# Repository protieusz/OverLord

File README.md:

# OverLord

Lotus layout unified split with 2x mcus & 2x trackballs.

# Sponsorship

Thank you  for sponsoring. For all you PCB/PCBA needs, PCBWay is the way to go. Good quality and customer service. During files submission, PCBWay take the time to check the BOM file and the component placement file to make sure that it is up to specs. If there are any issues, PCBWay will email back and inform the customer if there are any corrections that need to be made and also provide solutions for the customer. I highly recommend PCBWay. 

# Featured On KBDNews
https://kbd.news/OverLord-2477.html

# Detailed Summary

OverLord is a heavily modified version of Noraneko42L which has been blessed by darakuneko himself for the mod. Noraneko42L was originally designed by [darakuneko](https://github.com/darakuneko/Noraneko/tree/main/noraneko42l).

Entire PCB was designed using EasyEDA. ~I will upload a convert PCB file later.~ Be warn, the conversion might not be accurate and you might see a lot of DRC errors in KiCad but in EasyEDA it is ok since I have a working PCB right now.

~Right now at the moment still working out the kinks of getting the 2nd trackball to scroll and the orientation for the main mouse trackball. All the keys are working properly.~

A List Of Mods Made To The Original PCB file by darakuneko:

-Eliminate the extra 6th columns on each sides.

-Two circular holes were created in the middle that can accomodate 2x 25mm trackballs powered by 2x PMW3360 sensors.

-Base of the trackball holders with lens cut out is integrated into the top case with integrated 5mm switch plate. Top case sits flush with pcb.

-Full keyboard case was created to house the PCB.

-OverLord is powered by 2x RP2040 Core - As which you can get from AE.

-Shout out to miketronic from Fingerpunch discord for helping me with the QMK coding from his [BR/KN](https://github.com/miketronic/brkn-keyboard) and modifing the matrix to fit my OverLord. No suppport will be given since I just copy and paste.

-Shout to Doesntfazer of KeyboardDweebs.net for proofing reading and sanity checking my PCB schematic.

-Special thanks to Doesntfazer for fixing my QMK pointing device settings and finally got the scrolling ball to work.

-Use M2 brass hot inserts 3.2mm diameter and 4mm length for the M2 screws to secure the case. I forgot how long is my M2 screws are but they should be greater than 10mm so estimated around 14.6mm. Play around with and buy multiple M2 lenght screws.

-"Eye of Sauron" icon logo embross on the top case was borrowed from [Symbolon from the Noun Project](https://thenounproject.com/icon/eye-of-sauron-1007756/). "Eye of Sauron" logo was used to give it a dark lord theme.

-Both RP2040 Core-A mcus will be "linked" together by header pin wires instead of TRRS connector.

-Heads up if you are using Resin STEP files, resin print did not come out good, since the middle part was warped and the factory recommend to use 3.5mm for the bottom flat case area in order to prevent warping during print. Just use the PLA is more safer. Use the files at your own risk. You can modify the STEP files.

# Production Pics

# Test Fitting

# Renders

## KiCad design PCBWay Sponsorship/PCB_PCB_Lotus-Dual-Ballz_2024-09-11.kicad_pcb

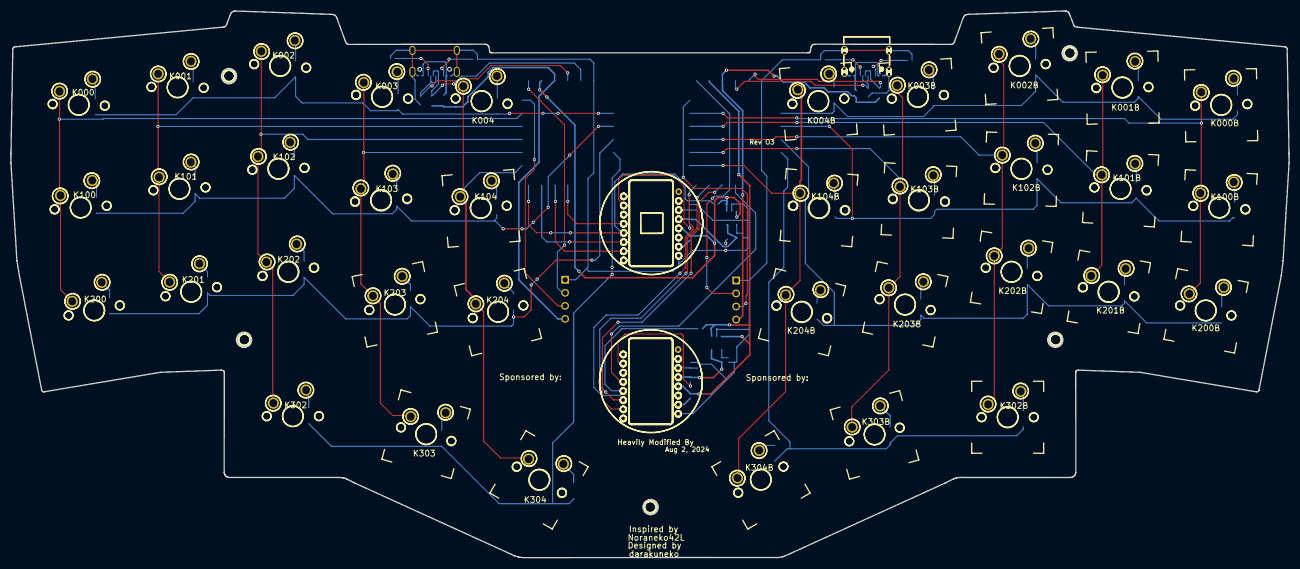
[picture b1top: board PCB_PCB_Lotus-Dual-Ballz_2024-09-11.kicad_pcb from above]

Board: 2 copper layers, 248.7 x 106.4 mm, 108 parts (0 on the bottom side), 92 nets.

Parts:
C17, C17B, C19, C19B, C20, C20B: 4.7uF; C0402
C18, C18B: 100nF; C0402
D000, D000B, D001, D001B, D002, D002B, D003, D003B, D004, D004B, D100, D100B, D101, D101B, D102, D102B, D103, D103B, D104, D104B, D200, D200B, D201, D201B, D202, D202B, D203, D203B, D204, D204B, D302, D302B, D303, D303B, D304, D304B: SM4007PL; SOD-123F_L2.8-W1.8-LS3.7-RD
D5, D11: PRTR5V0U2X,215; SOT-143_L2.9-W1.3-P1.92-LS2.3-BR
F1, F2: BSMD0805-020-15V; F0805
H1, H5: Header pins 1x04 1MM HOLES; 1X04 2.54MM HOLES HEADERS PINS 1MM HOLES
K000, K000B, K001, K001B, K002, K002B, K003, K003B, K004, K004B, K100, K100B, K101, K101B, K102, K102B, K103, K103B, K104, K104B, K200, K200B, K201, K201B, K202, K202B, K203, K203B, K204, K204B, K302, K302B, K303, K303B, K304, K304B: Switch; CHERRY_MX_100_MILLMAX
R1, R2, R3, R4: 5.1kΩ; R0402
R10, R10B, R12, R12B, R13, R13B: 10kΩ; R0402
R11, R11B: 39Ω; R0402
R14, R14B: 15kΩ; R0402
U1, U1B: RP2040-Core-A; RP2040-CORE-A
U7, U7B: PMW3360DM-T2QU; PMW3360DM-T2QU.PACK
U8, U8B: AP2127K-ADJTRG1; SOT-23-5_L3.0-W1.7-P0.95-LS2.8-BR
USBC1, USBC2: TYPE-C-31-M-12; USB-C_SMD-TYPE-C-31-M-12

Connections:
+2V: C20B.2, R11B.2, R14B.2, U7B.4, U8B.5
+2VL: C20.2, R11.2, R14.2, U7.4, U8.5
+3V3: C19B.2, R10B.2, R12B.2, U1B.15, U7B.5, U8B.1, U8B.3
+3V3L: C19.2, R10.2, R12.2, U1.15, U7.5, U8.1, U8.3
+5V: D5.4, F2.2, H1.4, U1B.16
+5VL: D11.4, F1.2, H5.4, U1.16
C18B_1: C17B.1, C18B.1, U7B.3
COL0L: K000.2, K100.2, K200.2, U1.12
COL0R: K000B.2, K100B.2, K200B.2, U1B.12
COL1L: K001.2, K101.2, K201.2, U1.11
COL1R: K001B.2, K101B.2, K201B.2, U1B.11
COL2L: K002.2, K102.2, K202.2, K302.2, U1.10
COL2R: K002B.2, K102B.2, K202B.2, K302B.2, U1B.10
COL3L: K003.2, K103.2, K203.2, K303.2, U1.9
COL3R: K003B.2, K103B.2, K203B.2, K303B.2, U1B.9
COL4L: K004.2, K104.2, K204.2, K304.2, U1.8
COL4R: K004B.2, K104B.2, K204B.2, K304B.2, U1B.8
CSL: U1.4, U7.13
CSR: U1B.4, U7B.13
D000B_2: D000B.2, K000B.1
D000_2: D000.2, K000.1
D001B_2: D001B.2, K001B.1
D001_2: D001.2, K001.1
D002B_2: D002B.2, K002B.1
D002_2: D002.2, K002.1
D003B_2: D003B.2, K003B.1
D003_2: D003.2, K003.1
D004B_2: D004B.2, K004B.1
D004_2: D004.2, K004.1
D100_2: D100.2, K100.1
D101B_2: D101B.2, K101B.1
D101_2: D101.2, K101.1
D102B_2: D102B.2, K102B.1
D102_2: D102.2, K102.1
D103B_2: D103B.2, K103B.1
D103_2: D103.2, K103.1
D104B_2: D104B.2, K104B.1
D104_2: D104.2, K104.1
D200B_2: D200B.2, K200B.1
D200_2: D200.2, K200.1
D201B_2: D201B.2, K201B.1
D201_2: D201.2, K201.1
D202B_2: D202B.2, K202B.1
D202_2: D202.2, K202.1
D203B_2: D203B.2, K203B.1
D203_2: D203.2, K203.1
D204B_2: D204B.2, K204B.1
D204_2: D204.2, K204.1
D302B_2: D302B.2, K302B.1
D302_2: D302.2, K302.1
D303B_2: D303B.2, K303B.1
D303_2: D303.2, K303.1
D304_2: D304.2, K304.1
D+L: D11.3, U1.18, USBC1.A6, USBC1.B6
D+R: D5.3, U1B.18, USBC2.A6, USBC2.B6
D-L: D11.2, U1.17, USBC1.A7, USBC1.B7
D-R: D5.2, U1B.17, USBC2.A7, USBC2.B7
GND: C17B.2, C18B.2, C19B.1, C20B.1, D5.1, H1.1, R3.1, R4.2, R13B.1, U1B.19, U7B.8, U8B.2, USBC2.0, USBC2.1, USBC2.2, USBC2.3, USBC2.A1, USBC2.A12, USBC2.B1, USBC2.B12
GNDL: C17.2, C18.2, C19.1, C20.1, D11.1, H5.1, R1.2, R2.1, R13.1, U1.19, U7.8, U8.2, USBC1.0, USBC1.1, USBC1.2, USBC1.3, USBC1.A1, USBC1.A12, USBC1.B1, USBC1.B12
K100B_1: D100B.2, K100B.1
K304B_1: D304B.2, K304B.1
MISOL: R12.1, U1.7, U7.12
MISOR: R12B.1, U1B.7, U7B.12
MOSIL: U1.6, U7.11
MOSIR: U1B.6, U7B.11
R1_1: R1.1, USBC1.A5
R2_2: R2.2, USBC1.B5
R10B_1: R10B.1, U7B.7
R11B_1: R11B.1, U7B.15
R14B_1: R13B.2, R14B.1, U8B.4
ROW0L: D000.1, D001.1, D002.1, D003.1, D004.1, U1.21
ROW0R: D000B.1, D001B.1, D002B.1, D003B.1, D004B.1, U1B.21
ROW1L: D100.1, D101.1, D102.1, D103.1, D104.1, U1.22
ROW1R: D100B.1, D101B.1, D102B.1, D103B.1, D104B.1, U1B.22
ROW2L: D200.1, D201.1, D202.1, D203.1, D204.1, U1.23
ROW2R: D200B.1, D201B.1, D202B.1, D203B.1, D204B.1, U1B.23
ROW3L: D302.1, D303.1, D304.1, U1.24
ROW3R: D302B.1, D303B.1, D304B.1, U1B.24
RXL: H5.2, U1.14
RXR: H1.2, U1B.14
SCKL: U1.5, U7.10
SCKR: U1B.5, U7B.10
TXL: H5.3, U1.13
TXR: H1.3, U1B.13
U7_3: C17.1, C18.1, U7.3
U7_7: R10.1, U7.7
U7_15: R11.1, U7.15
U8_4: R13.2, R14.1, U8.4
USBC2_A5: R4.1, USBC2.A5
USBC2_B5: R3.2, USBC2.B5
VBUSL: F1.1, USBC1.A4, USBC1.A9, USBC1.B4, USBC1.B9
VBUSR: F2.1, USBC2.A4, USBC2.A9, USBC2.B4, USBC2.B9

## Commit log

2024-04-18 QMK source
2024-04-19 Added keymaps folder
2024-08-18 QMK Firmware Left Scroll Right Mouse
2024-08-18 License
2024-08-19 STLs
2024-08-20 Case STEP files
2024-08-20 DXF layout
2024-08-20 Schematic
2024-09-12 Convert pcb file from EasyEda json file
2024-09-12 Updated the QMK working scrolling
2024-09-12 Updated firmware with working scroll
2024-09-12 Fix the volume keys
2024-09-12 fixed the volume keys
2024-09-12 Update LICENSE
